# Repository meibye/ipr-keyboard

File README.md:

# ipr-keyboard

IrisPen text-file ingestion to Bluetooth keyboard output on Raspberry Pi.

## Documentation

See:
- docs/README.md
- docs/architecture/ARCHITECTURE.md
- DEVICE_BRINGUP.md

## Current State

BLE HID over GATT stack using bt_hid_ble.service and bt_hid_agent_unified.service.

## Quick Start

```bash
sudo ./provision/provision_wizard.sh
```

## Directory Guide

- docs/ — all human-facing documentation
- src/ipr_keyboard/ — application
- scripts/ — operational scripts

## Notes

Start all cleanup and refactor work from docs/architecture/ARCHITECTURE.md

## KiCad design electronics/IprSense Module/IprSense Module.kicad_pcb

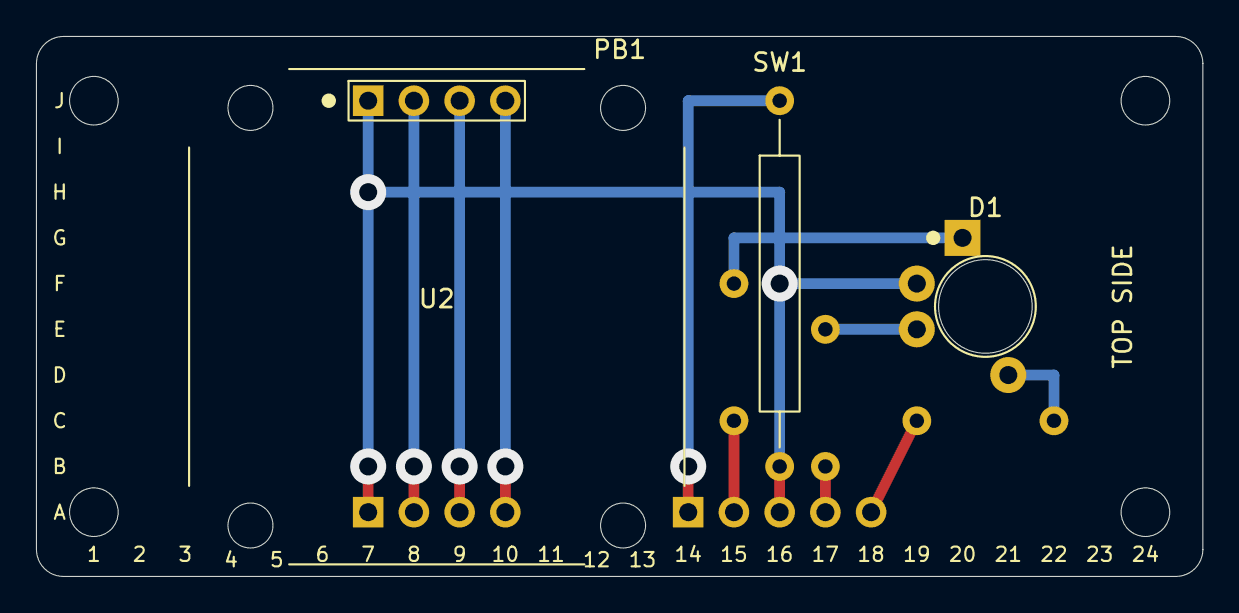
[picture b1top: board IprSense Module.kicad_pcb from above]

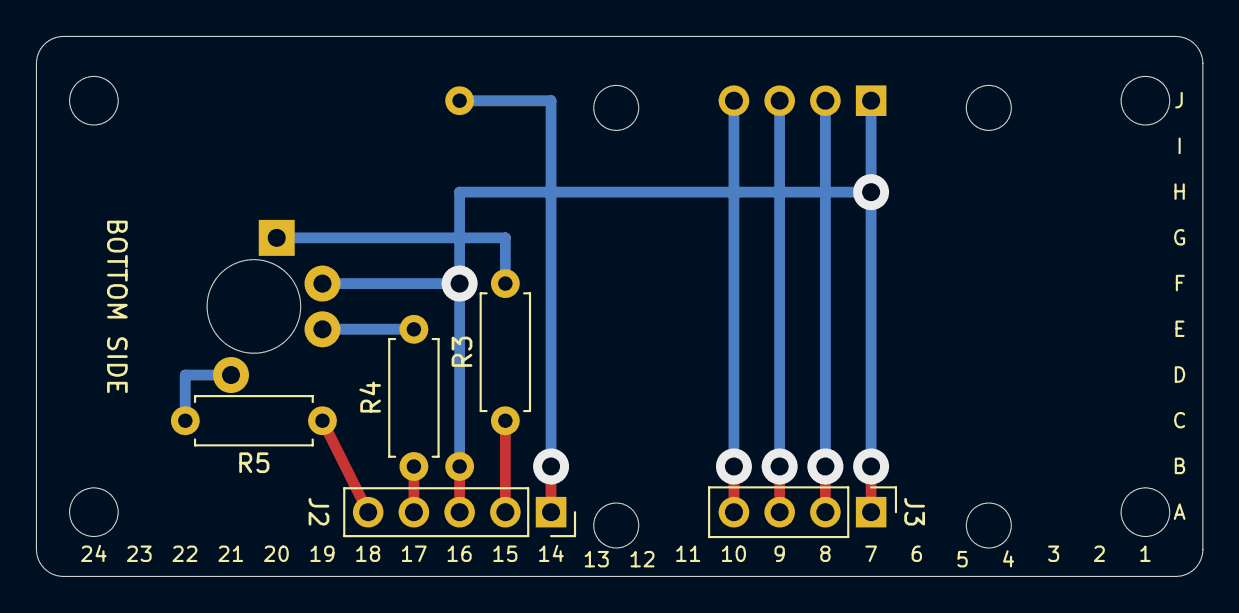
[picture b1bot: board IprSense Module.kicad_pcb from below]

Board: 2 copper layers, 64.8 x 30.0 mm, 9 parts (5 on the bottom side), 11 nets.

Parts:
D1: LED_RKGB; LED_D5.0mm-4_RGB_ReverseMount_Perfboard
J2: Conn_01x05; PinSocket_1x05_P2.54mm_Vertical
J3: Conn_01x04; PinHeader_1x04_P2.54mm_Vertical
PB1: Perfboard_10x24_P2.54mm_30x64.8mm
R3, R4: 150; R_Axial_DIN0207_L6.3mm_D2.5mm_P7.62mm_Horizontal
R5: 22; R_Axial_DIN0207_L6.3mm_D2.5mm_P7.62mm_Horizontal
SW1: SW_Reed; SW_Reed_Glass_L14mm_D2mm_P20.32mm_Horizontal
U2: OLED_JMD0.96D-1-I2C; OLED_0.96in_128x64_I2C_27.3x27.3mm_P2.54mm

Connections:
+3V3: J3.2, U2.2
/GPIO2/SDA1: J3.4, U2.4
/GPIO3/SCL1: J3.3, U2.3
/GPIO22: J2.2, R3.1
/GPIO23: J2.4, R4.1
/GPIO24: J2.5, R5.2
/GPIO27: J2.1, SW1.2
GND: D1.2, J2.3, J3.1, SW1.1, U2.1
unnamed: D1.4, R5.1
unnamed: D1.3, R4.2
unnamed: D1.1, R3.2

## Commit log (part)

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2025-12-26 Made executable
2025-12-26 Fix variable declaration for error and warning counts in verification script
2025-12-26 Enhance verification script: Add logging for service checks and warnings
2025-12-26 Refactor verification script: Remove redundant logging around service check increments
2025-12-26 Enhance provisioning script: Add logging for ssh-agent startup and SSH key addition
2025-12-26 Enhance provisioning script: Improve ssh-agent handling for user-specific SSH keys
2025-12-26 Enhance documentation: Add instructions for checking if branches are up to date
2025-12-26 Enhance documentation: Add instructions for comparing branches in Git
2025-12-27 Refactor service names in svc_status_monitor.py for clarity and consistency
2025-12-27 Enhance Bluetooth service: Use environment variable for device name and add connection status for paired devices
2025-12-27 Enhance main screen display: Add Bluetooth device information and improve service action handling in TUI
2025-12-27 Refactor svc_status_monitor.py: Remove unused configuration loading logic to streamline code
2025-12-27 Refactor svc_status_monitor.py: Remove unused functions and streamline main loop
    - Removed redundant function definitions and code blocks to simplify the script.
    - Consolidated service and device handling logic within the main loop.
    - Cleaned up unnecessary imports and variables to enhance readability and maintainability.
2025-12-27 Enhance svc_status_monitor.py: Add color support check for terminal and improve color handling for service and device status display
2025-12-31 Refactor BLE HID daemon installation script
    - Improved error handling with set -euo pipefail for better script robustness.
    - Streamlined the writing of the Python daemon script, focusing on clarity and maintainability.
    - Updated the HID service UUIDs to use minimal values for demonstration purposes.
    - Enhanced character mapping for Danish special characters.
    - Simplified the advertisement registration process and improved logging.
    - Added functionality to ensure the FIFO file is created if it doesn't exist.
2025-12-31 Enhance svc_status_monitor.py: Update service restart command to require sudo for improved permissions handling
2025-12-31 Enhance svc_status_monitor.py: Require sudo for service start, stop, and restart actions to improve permissions handling
2025-12-31 Enhance get_service_status function: Improve error handling for service status checks to differentiate between 'not loaded' and 'inactive' states.
2026-01-01 Add category and purpose comments to legacy Bluetooth service installation scripts
2026-01-01 Refactor service installation script: Simplify bt_hid_ble.service installation logic and improve logging for service unit creation.
2026-01-01 Improve advertisement properties for Windows compatibility: Ensure explicit discoverable and LE-only flags, and avoid duplication parsing issues.
2026-01-01 Refactor adapter discoverability logic: Clarify handling of classic discoverable based on controller mode to improve Windows pairing behavior.
2026-01-02 Add debugging options for Bluetooth agent and BLE daemon
2026-01-03 Update Bluetooth service and agent execution parameters: Modify ExecStart commands for improved functionality and compatibility.
2026-01-03 Enhance Bluetooth service installation script: Add environment file defaults, improve debug flag handling, and streamline service unit configurations for stability and performance.
2026-01-04 Update BLE installation script: Enable BLE backend by default and disable uinput backend for improved functionality.
2026-01-04 Refactor Bluetooth agent methods: Comment out unused pin code and passkey methods for cleaner code and improved maintainability. Enhance advertisement release logging and ensure Bluetooth cache is cl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
2026-01-05 Update Bluetooth installation script: Add Experimental=true to main.conf for LE GATT/advertising support. Modify ExecStart to include --experimental flag for improved functionality.
2026-01-05 Update Bluetooth agent service script: Modify ExecStartPre commands for improved execution and error handling.
2026-01-05 Update diagnostic script: Enhance advertising state check for BLE HID device visibility
2026-01-07 Extract service definitions and executables into separate files
2026-01-07 Add comprehensive README for service scripts directory
2026-01-07 Update main documentation to reference remote diagnostic scripts
    - Added reference to remote diagnostic scripts in main README.md
    - Added Remote Diagnostic Scripts section in scripts/README.md
    - Links to detailed diag/README.md for GitHub Copilot integration
2026-01-07 Update scripts/diag_pairing.sh and scripts/README.md for NoInputNoOutput capability
2026-01-07 Reorganize Bluetooth and diagnostic scripts into dedicated folders
2026-01-07 Fix remaining script path references in documentation and comments
2026-01-09 feat: Add local-only Copilot mode instructions and constraints
2026-01-11 feat: Add Bluetooth pairing playbook and diagnostic agent prompt; implement MCP enable/disable scripts
2026-01-13 feat: Add git user configuration and rebase option to bootstrap script and example env
2026-01-13 refactor: Remove backend configuration from service installation script and enhance error messages in BLE setup script
2026-01-14 fix: Update user creation command for non-interactive mode in debug tools script fix: Remove unused service from verification script
2026-01-25 feat: Refactor MCP setup and runner scripts for improved SSH integration and configuration management
2026-01-25 fix: Update warning message for public key input in Copilot debug tools script
2026-01-25 feat: Add status check for automation clone synchronization with origin
2026-01-25 feat: Create mcp.json for SSH server configuration and update setup script to determine repository root
2026-01-25 feat: Enhance MCP SSH runner with allowlist and whitelist support for improved command control
2026-01-31 refactor: Simplify MCP server configuration by removing redundant comments and ensuring consistent argument formatting
2026-01-31 refactor: Simplify key handling in Copilot debug tools by removing deprecated guard logic
2026-01-31 refactor: Remove deprecated MCP enable/disable scripts and clean up service list
2026-02-07 refactor: Update documentation for remote device access and usage guidance across multiple files
2026-02-11 refactor: Enhance bt_hid_agent_unified.service for improved Bluetooth stability and compatibility
2026-02-11 refactor: Comment out stability fix for adapter class setting in bt_hid_agent_unified.py
2026-02-13 refactor: Update version and USB identifiers in service installation script
2026-02-15 feat: Add task to launch Local Claude with GPU check and create launch script
2026-02-17 cleanup: align runtime/docs/scripts with BLE-only architecture
2026-02-25 Normalize line endings to LF
2026-02-25 cleanup: Remove unnecessary closing brace from bt_kb_send script
2026-02-25 feat: Add additional punctuation mappings for HID keyboard support
2026-02-27 feat: Implement auto-unblock for Bluetooth if soft-blocked
2026-04-10 Made executbale
2026-04-11 fix: Correct log level constant and update timestamp in BLE capture log
2026-04-12 fix: Update version number in bt_hid_ble_daemon.py
2026-04-12 fix: Update version timestamps in bt_hid_ble_daemon.py and ble_capture_debug_cmd.ps1; refactor parameter name in run_ble_roundtrip_mcp.ps1
2026-04-12 fix: Update version timestamps in ble_capture_debug_cmd.ps1; add reports directory to .gitignore; refactor parameters in update-version.ps1; enhance run_ble_roundtrip_mcp.ps1 with local output path; 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
2026-04-12 fix: Update version timestamp in bt_hid_ble_daemon.py
2026-04-12 fix: Update BLE service description and enhance logging timestamps in capture debug script
2026-04-12 fix: Update version timestamps and enhance comparison modes in BLE capture scripts
2026-04-12 fix: Update version timestamps and enhance character coverage documentation in Danish MX Keys test files
2026-04-12 feat: Enhance web server functionality with new status page and improved index links
2026-04-12 feat: Add version logging to Bluetooth, USB, and web modules
2026-04-12 feat: Update version number and refactor log_version_info function to use config_manager
2026-04-17 docs: add PR 2 Markdown audit — classify files for web dashboard impact
    Agent-Logs-Url: https://github.com/meibye/ipr-keyboard/sessions/a417e01f-b95f-4366-8efa-f4f37038d263
2026-04-17 fix: further code review cleanup in api.py
    - Remove unused _run_cmd helper and List import
    - Fix SSE stream deque wrap-around bug: track last seen event ID
    instead of buffer length so events are never missed or duplicated
    when the 200-event circular buffer rolls over
    Agent-Logs-Url: https://github.com/meibye/ipr-keyboard/sessions/13e3efcb-7163-45e3-8a23-2b4f17194923
2026-04-17 docs: move ARCHITECTURE.md into docs/architecture
2026-04-17 docs: move development workflow
2026-04-17 docs: remove moved file
2026-04-26 feat: Enhance provisioning and verification scripts, add software version endpoint and dashboard display
2026-04-27 feat: Update configuration management to include dynamic pen folder options and logging level adjustments
2026-04-27 feat: Enhance configuration management with new network settings and update dashboard for device info
2026-04-29 feat: Enhance user management by ensuring at least one admin account exists and backfilling is_admin field
2026-05-08 feat: Add default configuration file and remove users.json for improved security
2026-05-30 feat: Add scheduling skills to permissions in settings
2026-05-31 feat: Enhance setup script with grestore_ipr function and update bashrc aliases
2026-05-31 feat: Implement user management features including password change, admin status toggle, and user list display
2026-05-31 refactor: Update script categories and purposes for better clarity and organization
2026-06-01 Add setup provisioning interface and enhance web UI
    - Introduced a new setup blueprint for device provisioning at the /setup endpoint, allowing management of Wi-Fi connections and system status.
    - Implemented HTTP Basic Authentication for the setup interface, securing access to sensitive operations.
    - Added new routes for viewing logs, managing Wi-Fi connections, and performing system actions (reboot/shutdown).
    - Created dedicated templates and styles for the setup interface, ensuring a consistent user experience across the web application.
    - Updated existing templates to utilize shared styles, improving maintainability and visual consistency.
    - Enhanced CSS styles for legacy pages and the n
2026-06-01 feat: Enhance journal viewer with toggleable line wrapping functionality
2026-06-01 feat: Implement TLS certificate renewal process and integrate into provisioning service
2026-06-02 feat: Update .gitattributes to include additional file types for LF normalization
2026-06-07 feat: Update GPIO monitoring process with user prompts and improved handling
